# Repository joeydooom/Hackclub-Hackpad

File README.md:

# Hackclub-Hackpad
For hackclub project
  
Bill of materials:
1x Bottom case
1x Top case
1x PCB grant
1x Soldering iron grant
Seeed XIAO RP2040 microcontroller	1
MX-style mechanical switches	6
Blank DSA keycaps	6
M3×16mm screws	4
M3×5×4mm heatset inserts	4

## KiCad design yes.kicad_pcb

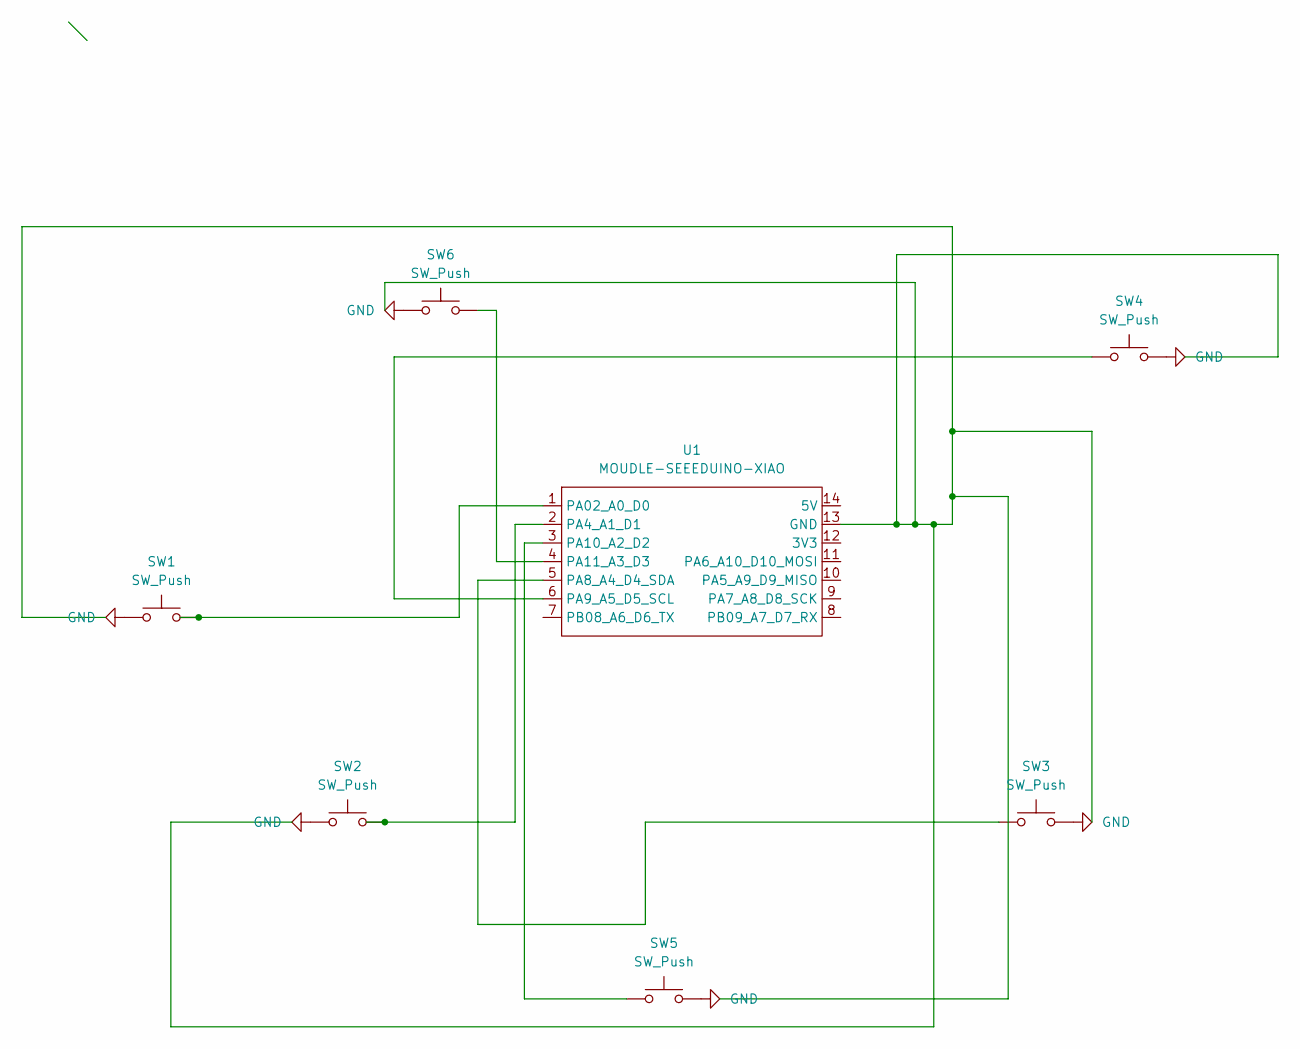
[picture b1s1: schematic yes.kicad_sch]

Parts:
SW1, SW2, SW3, SW4, SW5, SW6: SW_Push; SW_Cherry_MX_1.00u_PCB
U1: MOUDLE-SEEEDUINO-XIAO; XIAO-Generic-Hybrid-14P-2.54-21X17.8MM

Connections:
GND: SW1.1, SW2.1, SW3.2, SW4.2, SW5.2, SW6.1
unnamed: SW1.2, U1.1 (PA02_A0_D0)
unnamed: SW2.2, U1.2 (PA4_A1_D1)
unnamed: SW3.1, U1.5 (PA8_A4_D4_SDA)
unnamed: SW4.1, U1.6 (PA9_A5_D5_SCL)
unnamed: SW5.1, U1.3 (PA10_A2_D2)
unnamed: SW6.2, U1.4 (PA11_A3_D3)

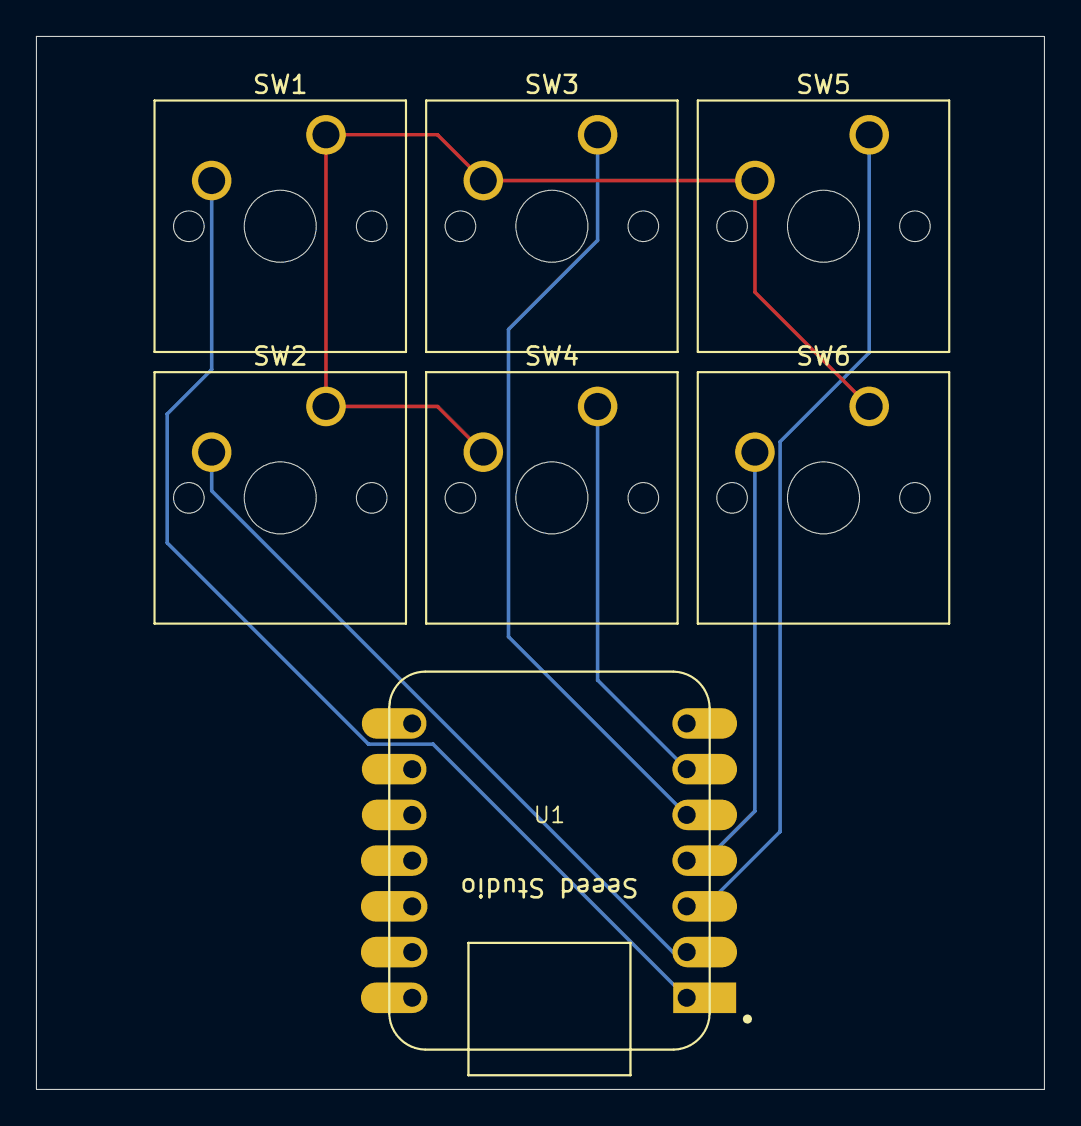
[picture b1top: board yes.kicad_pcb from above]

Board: 2 copper layers, 56.0 x 58.5 mm, 7 parts (0 on the bottom side), 7 nets.

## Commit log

2026-06-03 Update README with images and materials list
    Added images and bill of materials to README.
